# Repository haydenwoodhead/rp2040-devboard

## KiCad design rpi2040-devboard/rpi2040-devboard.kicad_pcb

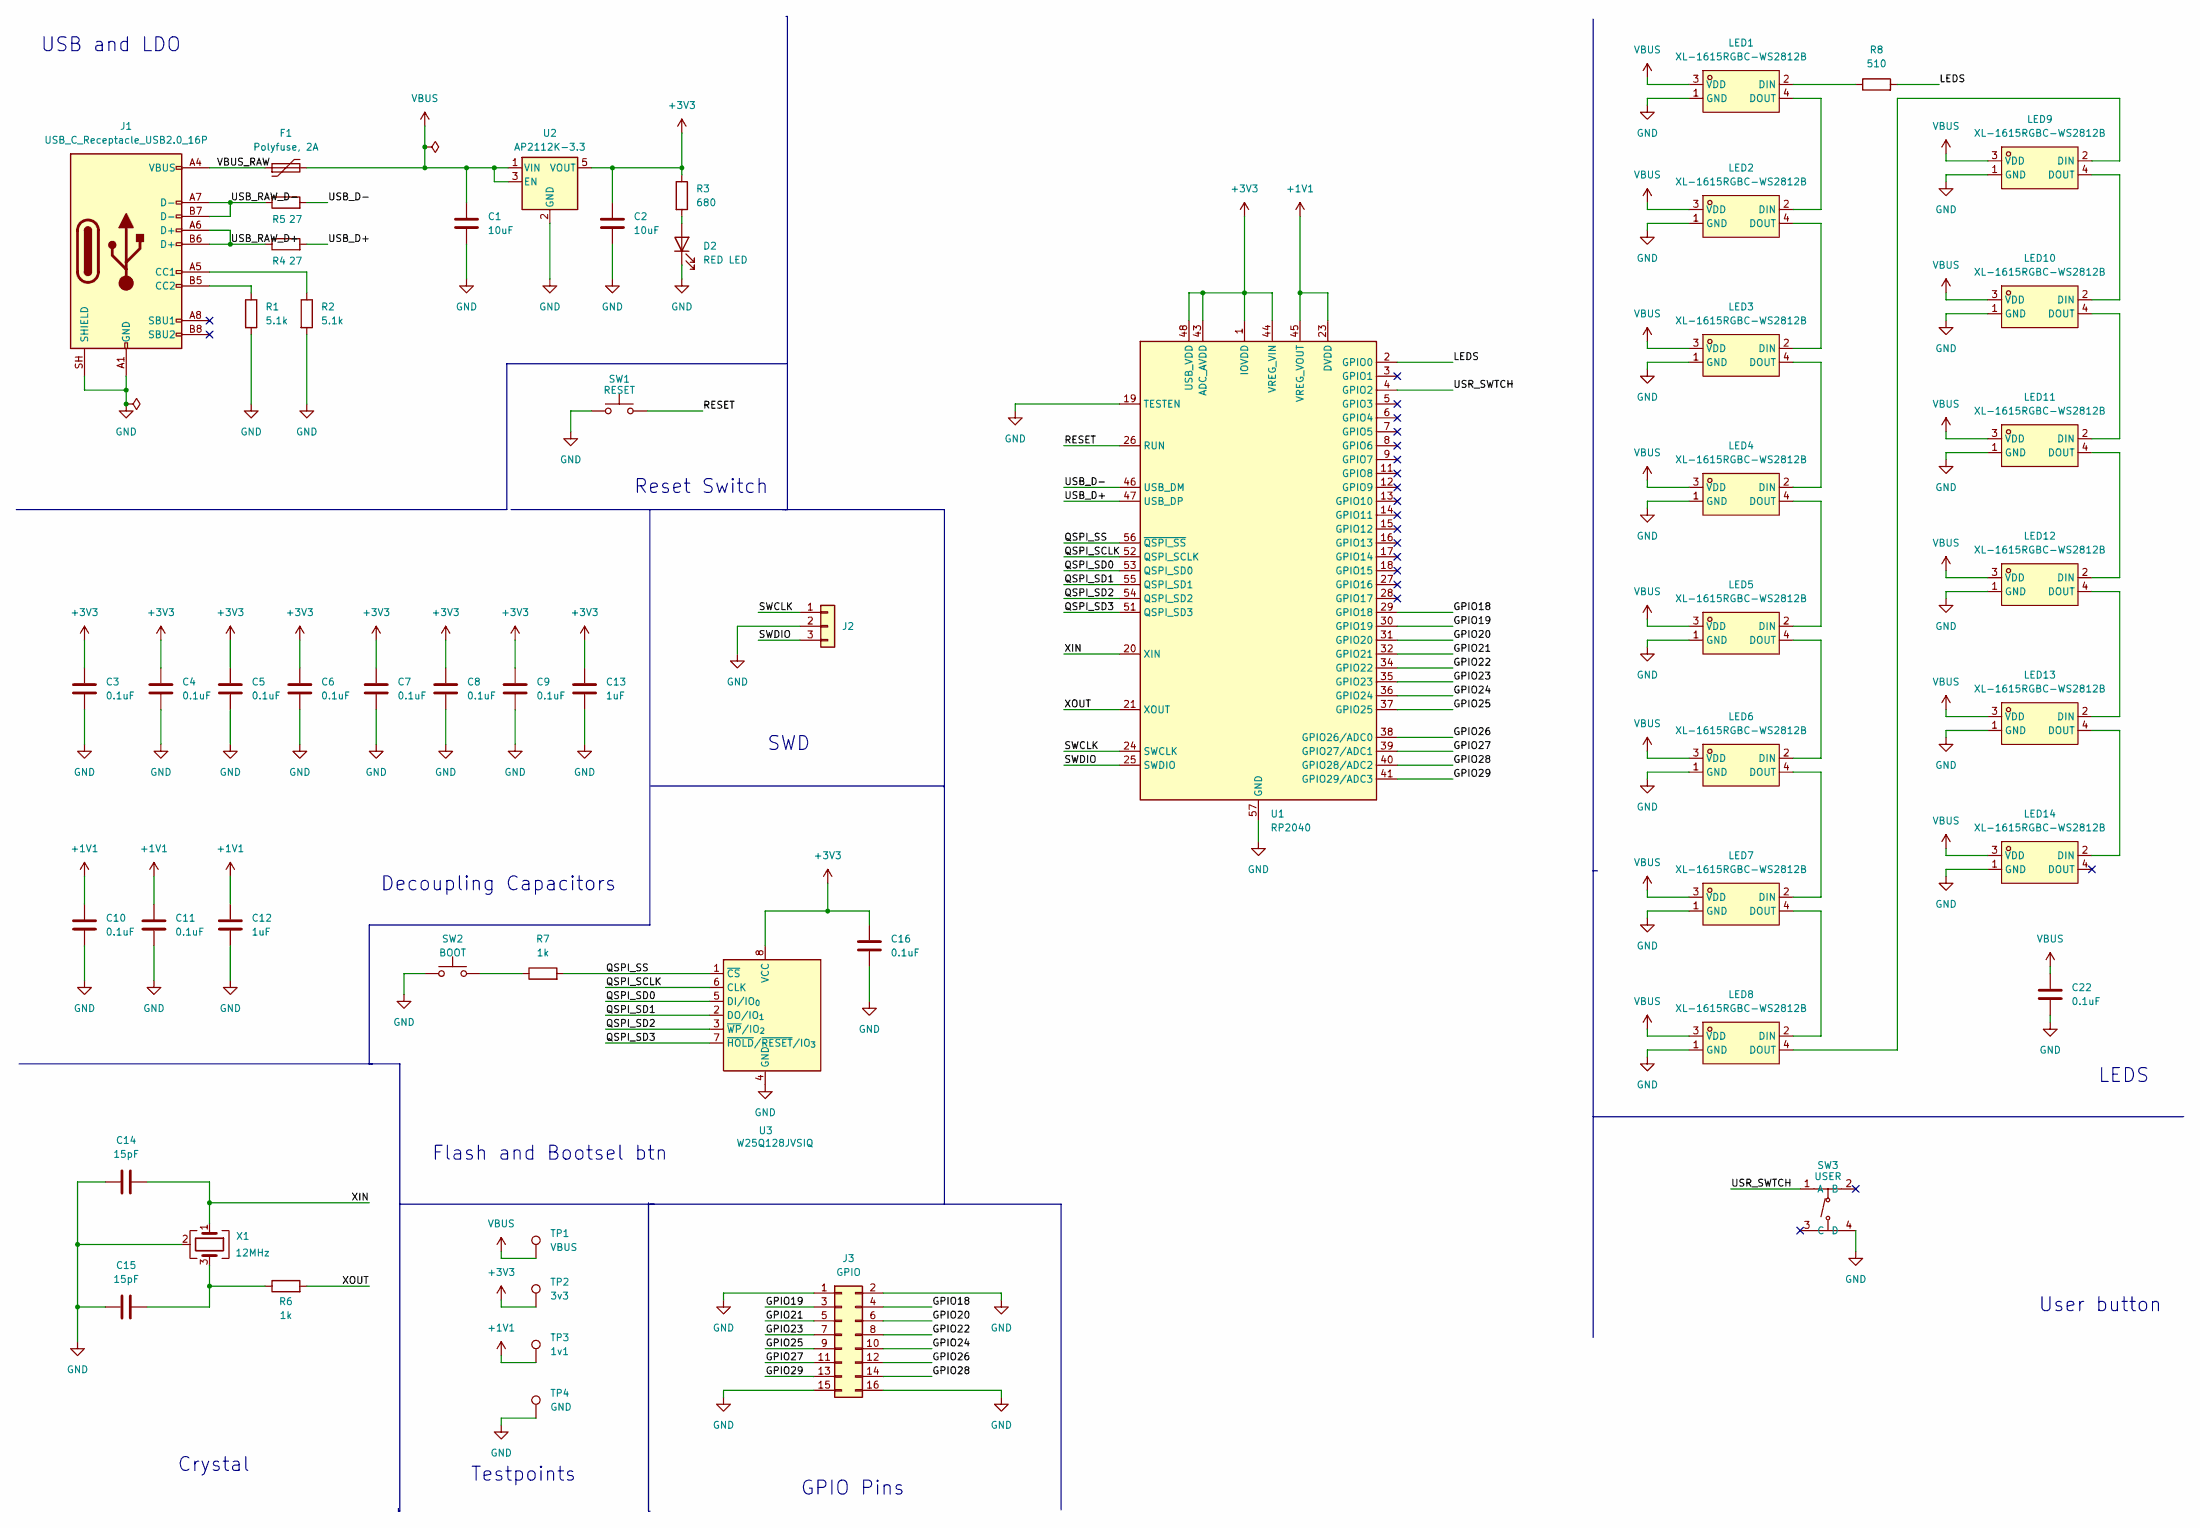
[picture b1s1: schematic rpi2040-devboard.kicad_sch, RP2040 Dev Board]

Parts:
C1, C2: 10uF; C_0603_1608Metric; MPN CL10A106MA8NRNC; LCSC C96446
C3, C4, C5, C6, C7, C8, C9, C10, C11, C16, C22: 0.1uF; C_0603_1608Metric; MPN CC0603KRX7R9BB104; LCSC C14663
C12, C13: 1uF; C_0603_1608Metric; MPN CC0603KRX5R9BB105; LCSC C128624
C14, C15: 15pF; C_0603_1608Metric; MPN CL10C150JB8NNNC; LCSC C1644
D2: RED LED; LED_0603_1608Metric; MPN KT-0603R; LCSC C2286
F1: Polyfuse, 2A; Fuse_1206_3216Metric; MPN SMD1206-200/06N; LCSC C6165195
J1: USB_C_Receptacle_USB2.0_16P; USB_C_Receptacle_HRO_TYPE-C-31-M-12; MPN TYPE-C-31-M-12; LCSC C165948
J2: SWD; PinHeader_1x03_P2.54mm_Vertical
J3: GPIO; PinHeader_2x08_P2.54mm_Vertical
LED1, LED2, LED3, LED4, LED5, LED6, LED7, LED8, LED9, LED10, LED11, LED12, LED13, LED14: XL-1615RGBC-WS2812B; LED-SMD_4P-L1.6-W1.5_XL-1615RGBC-WS2812B-1; MPN XL-1615RGBC-2812B; LCSC Part C5349954
R1, R2: 5.1k; R_0603_1608Metric; MPN 0603WAF5101T5E; LCSC C23186
R3: 680; R_0603_1608Metric; MPN 0603WAF6800T5E; LCSC C23228
R4, R5: 27; R_0603_1608Metric; MPN CQ03WAF270JT5E; LCSC C2770847
R6, R7: 1k; R_0603_1608Metric; MPN RC0603FR-071KL; LCSC C22548
R8: 510; R_0603_1608Metric; MPN 0603WAF5100T5E; LCSC C23193
SW1: RESET; SW_SPST_TS-1088-xR020; MPN TS-1088-AR02016; LCSC C720477
SW2: BOOT; SW_SPST_TS-1088-xR020; MPN TS-1088-AR02016; LCSC C720477
SW3: USER; SW-SMD_4P-L5.1-W5.1-P3.70-LS6.5-TL_H1.5; MPN TS-1187A-B-A-B; LCSC Part C318884
TP1: VBUS; TestPoint_Pad_D1.5mm
TP2: 3v3; TestPoint_Pad_D1.5mm
TP3: 1v1; TestPoint_Pad_D1.5mm
TP4: GND; TestPoint_Pad_D1.5mm
U1: RP2040; QFN-56-1EP_7x7mm_P0.4mm_EP3.2x3.2mm; MPN RP2040; LCSC C2040
U2: AP2112K-3.3; SOT-23-5; MPN AP2112K-3.3TRG1; LCSC C51118
U3: W25Q128JVSIQ; SOIC-8_5.3x5.3mm_P1.27mm; MPN W25Q128JVSIQ; LCSC C113767
X1: 12MHz; Crystal_SMD_3225-4Pin_3.2x2.5mm; tolerance 30ppm; part_uid RP-01G8X7-GS352B; LCSC C20625731

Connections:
+1V1: C10.1, C11.1, C12.1, TP3.1 (1_1), U1.23 (DVDD), U1.45 (VREG_VOUT), U1.50 (DVDD)
+3V3: C2.1, C3.1, C4.1, C5.1, C6.1, C7.1, C8.1, C9.1, C13.1, C16.1, R3.1, TP2.1 (1_1), U1.1 (IOVDD), U1.10 (IOVDD), U1.22 (IOVDD), U1.33 (IOVDD), U1.42 (IOVDD), U1.43 (ADC_AVDD), U1.44 (VREG_VIN), U1.48 (USB_VDD), U1.49 (IOVDD), U2.5 (VOUT), U3.8 (VCC)
/GPIO18: J3.4, U1.29 (GPIO18)
/GPIO19: J3.3, U1.30 (GPIO19)
/GPIO20: J3.6, U1.31 (GPIO20)
/GPIO21: J3.5, U1.32 (GPIO21)
/GPIO22: J3.8, U1.34 (GPIO22)
/GPIO23: J3.7, U1.35 (GPIO23)
/GPIO24: J3.10, U1.36 (GPIO24)
/GPIO25: J3.9, U1.37 (GPIO25)
/GPIO26: J3.12, U1.38 (GPIO26/ADC0)
/GPIO27: J3.11, U1.39 (GPIO27/ADC1)
/GPIO28: J3.14, U1.40 (GPIO28/ADC2)
/GPIO29: J3.13, U1.41 (GPIO29/ADC3)
/LEDS: R8.2, U1.2 (GPIO0)
/QSPI_SCLK: U1.52 (QSPI_SCLK), U3.6 (CLK)
/QSPI_SD0: U1.53 (QSPI_SD0), U3.5 (DI/IO_{0})
/QSPI_SD1: U1.55 (QSPI_SD1), U3.2 (DO/IO_{1})
/QSPI_SD2: U1.54 (QSPI_SD2), U3.3 (~WP/IO_{2})
/QSPI_SD3: U1.51 (QSPI_SD3), U3.7 (~HOLD/~RESET/IO_{3})
/QSPI_SS: R7.2, U1.56 (~QSPI_SS), U3.1 (~CS)
/RESET: SW1.2, U1.26 (RUN)
/SWCLK: J2.1, U1.24 (SWCLK)
/SWDIO: J2.3, U1.25 (SWDIO)
/USB_D+: R4.2, U1.47 (USB_DP)
/USB_D-: R5.2, U1.46 (USB_DM)
/USB_RAW_D+: J1.A6 (D+), J1.B6 (D+), R4.1
/USB_RAW_D-: J1.A7 (D-), J1.B7 (D-), R5.1
/USR_SWTCH: SW3.1 (A), U1.4 (GPIO2)
/VBUS_RAW: F1.1, J1.A4 (VBUS), J1.A9 (VBUS), J1.B4 (VBUS), J1.B9 (VBUS)
/XIN: C14.2, U1.20 (XIN), X1.1
/XOUT: R6.2, U1.21 (XOUT)
GND: C1.2, C2.2, C3.2, C4.2, C5.2, C6.2, C7.2, C8.2, C9.2, C10.2, C11.2, C12.2, C13.2, C14.1, C15.1, C16.2, C22.2, D2.1 (K), J1.A1 (GND), J1.A12 (GND), J1.B1 (GND), J1.B12 (GND), J1.SH (SHIELD), J2.2, J3.1, J3.2, J3.15, J3.16, LED1.1 (GND), LED2.1 (GND), LED3.1 (GND), LED4.1 (GND), LED5.1 (GND), LED6.1 (GND), LED7.1 (GND), LED8.1 (GND), LED9.1 (GND), LED10.1 (GND), LED11.1 (GND), LED12.1 (GND), LED13.1 (GND), LED14.1 (GND), R1.2, R2.2, SW1.1, SW2.1, SW3.4 (D), TP4.1 (1_1), U1.19 (TESTEN), U1.57 (GND), U2.2 (GND), U3.4 (GND), X1.2 (G), X1.4 (G)
unnamed: C15.2, R6.1, X1.3
unnamed: D2.2 (A), R3.2
unnamed: J1.A5 (CC1), R2.1
unnamed: J1.B5 (CC2), R1.1
unnamed: LED1.2 (DIN), R8.1
unnamed: LED1.4 (DOUT), LED2.2 (DIN)
unnamed: LED2.4 (DOUT), LED3.2 (DIN)
unnamed: LED3.4 (DOUT), LED4.2 (DIN)
unnamed: LED4.4 (DOUT), LED5.2 (DIN)
unnamed: LED5.4 (DOUT), LED6.2 (DIN)
unnamed: LED6.4 (DOUT), LED7.2 (DIN)
unnamed: LED7.4 (DOUT), LED8.2 (DIN)
unnamed: LED8.4 (DOUT), LED9.2 (DIN)
unnamed: LED9.4 (DOUT), LED10.2 (DIN)
unnamed: LED10.4 (DOUT), LED11.2 (DIN)
unnamed: LED11.4 (DOUT), LED12.2 (DIN)
unnamed: LED12.4 (DOUT), LED13.2 (DIN)
unnamed: LED13.4 (DOUT), LED14.2 (DIN)
unnamed: R7.1, SW2.2
VBUS: C1.1, C22.1, F1.2, LED1.3 (VDD), LED2.3 (VDD), LED3.3 (VDD), LED4.3 (VDD), LED5.3 (VDD), LED6.3 (VDD), LED7.3 (VDD), LED8.3 (VDD), LED9.3 (VDD), LED10.3 (VDD), LED11.3 (VDD), LED12.3 (VDD), LED13.3 (VDD), LED14.3 (VDD), TP1.1 (1_1), U2.1 (VIN), U2.3 (EN)

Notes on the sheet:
LEDS
User button
GPIO Pins
USB and LDO
SWD
Testpoints
Flash and Bootsel btn
Decoupling Capacitors
Crystal
Reset Switch

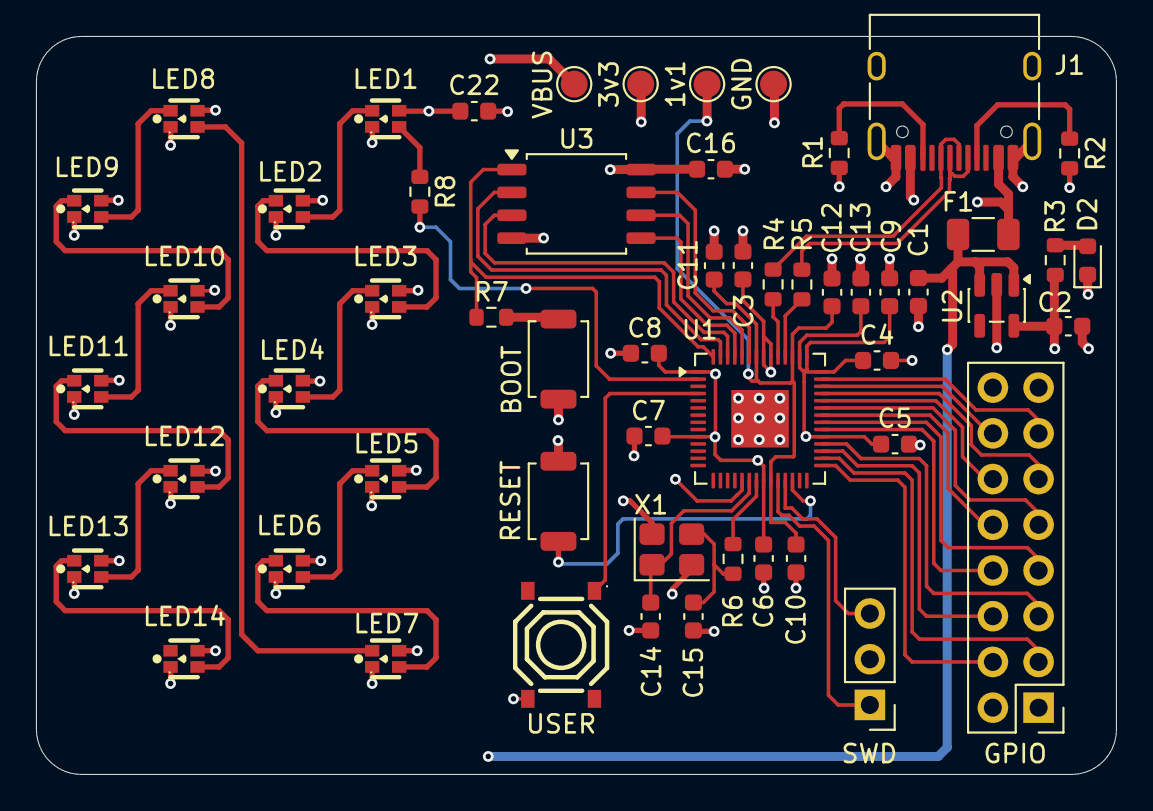
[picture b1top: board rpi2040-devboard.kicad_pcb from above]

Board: 4 copper layers, 60.0 x 41.0 mm, 55 parts (0 on the bottom side), 53 nets.

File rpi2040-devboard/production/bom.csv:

Designator,Footprint,Quantity,Value,LCSC Part #
"C1, C2",0603,2,10uF,C96446
"C10, C11, C16, C22, C3, C4, C5, C6, C7, C8, C9",0603,11,0.1uF,C14663
"C12, C13",0603,2,1uF,C128624
"C14, C15",0603,2,15pF,C1644
D2,0603,1,RED LED,C2286
F1,1206,1,"Polyfuse, 2A",C6165195
J1,USB_C_Receptacle_HRO_TYPE-C-31-M-12,1,USB_C_Receptacle_USB2.0_16P,C165948
J2,PinHeader_1x03_P2.54mm_Vertical,1,SWD,
J3,PinHeader_2x08_P2.54mm_Vertical,1,GPIO,
"LED1, LED10, LED11, LED12, LED13, LED14, LED2, LED3, LED4, LED5, LED6, LED7, LED8, LED9",LED-SMD_4P-L1.6-W1.5_XL-1615RGBC-WS2812B-1,14,XL-1615RGBC-WS2812B,C5349954
"R1, R2",0603,2,5.1k,C23186
R3,0603,1,680,C23228
"R4, R5",0603,2,27,C2770847
"R6, R7",0603,2,1k,C22548
R8,0603,1,510,C23193
SW1,SW_SPST_TS-1088-xR020,1,RESET,C720477
SW2,SW_SPST_TS-1088-xR020,1,BOOT,C720477
SW3,SW-SMD_4P-L5.1-W5.1-P3.70-LS6.5-TL_H1.5,1,USER,C318884
TP1,TestPoint_Pad_D1.5mm,1,VBUS,
TP2,TestPoint_Pad_D1.5mm,1,3v3,
TP3,TestPoint_Pad_D1.5mm,1,1v1,
TP4,TestPoint_Pad_D1.5mm,1,GND,
U1,QFN-56-1EP_7x7mm_P0.4mm_EP3.2x3.2mm,1,RP2040,C2040
U2,SOT-23-5,1,AP2112K-3.3,C51118
U3,SOIC-8_5.3x5.3mm_P1.27mm,1,W25Q128JVSIQ,C113767
X1,Crystal_SMD_3225-4Pin_3.2x2.5mm,1,12MHz,C20625731
